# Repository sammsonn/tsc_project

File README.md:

# Nume: Samson Alexandru-Valentin
# Grupa: 332CC

## 1. Descriere Generala:
Acest repository contine fisierele de design hardware pentru proiectul OpenBook, un e-book reader ieftin si open source, generate in cadrul fazei EVT. Obiectivul acestei faze a fost transformarea specificatiilor de sistem intr-un design hardware functional si integrat mecanic, pregatit pentru fabricarea primelor prototipuri.

## Etapele Initiale ale Dezvoltarii EVT (Rezumat)

Dezvoltarea designului livrat aici a urmat cativa pasi cheie:

1.  **Clarificarea Specificatiilor si Planificarea:** Am inceput prin analiza detaliata a specificatiilor primite de la Arhitectul de Sistem pentru a intelege complet cerintele functionale, de performanta si de cost. Am adresat intrebari pentru clarificarea oricaror ambiguitati si am stabilit un plan de lucru initial. Tot in aceasta etapa am configurat mediul de dezvoltare in Fusion si repository-ul Git.

2.  **Selectia Componentelor si Crearea Librariilor:** Pe baza specificatiilor, am selectat componentele electronice specifice (Part Numbers), acordand o atentie deosebita costului, disponibilitatii pe termen lung si performantei. Pentru fiecare componenta aleasa, am creat sau validat librariile necesare in Fusion 360: simbolul schematic, footprint-ul PCB (conform datasheet) si, unde a fost posibil, modelul 3D asociat. Am inceput compilarea unui Bill of Materials (BOM) preliminar.

3.  **Captura Schematica (Schematic Capture):** Folosind librariile create, am desenat diagrama schematica in Fusion 360. Aceasta reprezinta conexiunile logice dintre toate componentele electronice. Am structurat schema pe module functionale (ex: Alimentare, Procesor, Memorie, Interfata Display, etc.) pentru claritate si am rulat verificari ERC (Electrical Rule Check) pentru a detecta erori de baza.

4.  **Proiectarea PCB (PCB Layout) - Faza Initiala:** Am inceput transpunerea schemei intr-un layout fizic pe placa de circuit imprimat (PCB). Aceasta a inclus definirea conturului placii (conform dimensiunilor impuse de carcasa), definirea structurii straturilor (layer stackup) si plasarea initiala a componentelor critice (conectori, circuite integrate principale, componente cu constrangeri mecanice), tinand cont de fluxul de semnal si constrangerile carcasei.

5.  **Modelare 3D si Integrare Mecanica Preliminara:** in paralel cu layout-ul PCB, am creat modele 3D simplificate, dar dimensional corecte, pentru elementele non-PCB majore (Display E-Ink, Baterie LiPo). Am inceput asamblarea virtuala in Fusion, combinand modelul 3D al PCB-ului (cu componentele plasate), modelele display-ului si bateriei, si modelul 3D al carcasei (primit) pentru a verifica potrivirea generala si a identifica potentiale conflicte de spatiu.

## 2. Diagrama Bloc

## 3. BOM - Bill of Materials
| Device | Value | Check_Price | Datasheet |
|--------|-------|-------------|-----------|
| ADAFRUIT_LEDCHIP-LED0603 | - | [Link](https://www.snapeda.com/parts/KP-1608SURCK/Kingbright/view-part/?ref=search&t=LED%200603) | [Link](https://www.snapeda.com/parts/KP-1608SURCK/Kingbright/datasheet/) |
| SJ | - | [Link](https://grabcad.com/library/solder-jumpers-1) | [Link](https://grabcad.com/library/solder-jumpers-1) |
| EAGLE-LTSPICE_C | 0.1uF/50V | [Link](https://componentsearchengine.com/part-view/CC0402MRX5R5BB106/YAGEO) | [Link](https://componentsearchengine.com/Datasheets/2/CC0402MRX5R5BB106.pdf) |
| ESP32_WROVER_EAGLE-LTSPICE_R | 0.47 | [Link](https://componentsearchengine.com/part-view/R0402%201%25%20100%20K%20(RC0402FR-07100KL)/YAGEO) | [Link](https://www.yageo.com/upload/media/product/products/datasheet/rchip/PYu-RC_Group_51_RoHS_L_12.pdf) |
| ESP32_WROVER_EAGLE-LTSPICE_R | 100K | [Link](https://componentsearchengine.com/part-view/R0402%201%25%20100%20K%20(RC0402FR-07100KL)/YAGEO) | [Link](https://www.yageo.com/upload/media/product/products/datasheet/rchip/PYu-RC_Group_51_RoHS_L_12.pdf) |
| EAGLE-LTSPICE_C | 100nF | [Link](https://componentsearchengine.com/part-view/CC0402MRX5R5BB106/YAGEO) | [Link](https://componentsearchengine.com/Datasheets/2/CC0402MRX5R5BB106.pdf) |
| RCL_CPOL-EUCT3528 | 100uF TANT | [Link](https://www.snapeda.com/parts/TAJB475K025RNJ/AVX/view-part/?ref=dk&t=capacitor%203528&con_ref=None) | [Link](https://s3.amazonaws.com/snapeda/datasheet/TAJB475K025RNJ_AVX.pdf) |
| ESP32_WROVER_EAGLE-LTSPICE_R | 10K | [Link](https://componentsearchengine.com/part-view/R0402%201%25%20100%20K%20(RC0402FR-07100KL)/YAGEO) | [Link](https://www.yageo.com/upload/media/product/products/datasheet/rchip/PYu-RC_Group_51_RoHS_L_12.pdf) |
| EAGLE-LTSPICE_C | 10uF | [Link](https://componentsearchengine.com/part-view/CC0402MRX5R5BB106/YAGEO) | [Link](https://componentsearchengine.com/Datasheets/2/CC0402MRX5R5BB106.pdf) |
| 112A-TAAR-R03_ATTEND | 112A-TAAR-R03_ATTEND | [Link](https://store.comet.srl.ro/Catalogue/Product/43497/) | [Link](https://store.comet.bg/download-file.php?id=8824) |
| ESP32_WROVER_EAGLE-LTSPICE_R | 15 | [Link](https://componentsearchengine.com/part-view/R0402%201%25%20100%20K%20(RC0402FR-07100KL)/YAGEO) | [Link](https://www.yageo.com/upload/media/product/products/datasheet/rchip/PYu-RC_Group_51_RoHS_L_12.pdf) |
| EAGLE-LTSPICE_C | 1uF | [Link](https://componentsearchengine.com/part-view/CC0402MRX5R5BB106/YAGEO) | [Link](https://componentsearchengine.com/Datasheets/2/CC0402MRX5R5BB106.pdf) |
| EAGLE-LTSPICE_C | 1uF/50V | [Link](https://componentsearchengine.com/part-view/CC0402MRX5R5BB106/YAGEO) | [Link](https://componentsearchengine.com/Datasheets/2/CC0402MRX5R5BB106.pdf) |
| ESP32_WROVER_EAGLE-LTSPICE_R | 2.2 | [Link](https://componentsearchengine.com/part-view/R0402%201%25%20100%20K%20(RC0402FR-07100KL)/YAGEO) | [Link](https://www.yageo.com/upload/media/product/products/datasheet/rchip/PYu-RC_Group_51_RoHS_L_12.pdf) |
| ESP32_WROVER_EAGLE-LTSPICE_R | 200 | [Link](https://componentsearchengine.com/part-view/R0402%201%25%20100%20K%20(RC0402FR-07100KL)/YAGEO) | [Link](https://www.yageo.com/upload/media/product/products/datasheet/rchip/PYu-RC_Group_51_RoHS_L_12.pdf) |
| ESP32_WROVER_SPARKFUN-DISCRETESEMI_MOSFET_PCH-DMG2305UX-7 | 20V/4.2A/52m?/1.4W | [Link](https://componentsearchengine.com/part-view/DMG2305UX-7/Diodes%20Incorporated) | [Link](https://www.diodes.com//assets/Datasheets/DMG2305UX.pdf) |
| ESP32_WROVER_EAGLE-LTSPICE_R | 2K | [Link](https://componentsearchengine.com/part-view/R0402%201%25%20100%20K%20(RC0402FR-07100KL)/YAGEO) | [Link](https://www.yageo.com/upload/media/product/products/datasheet/rchip/PYu-RC_Group_51_RoHS_L_12.pdf) |
| EAGLE-LTSPICE_C | 4.7uF | [Link](https://componentsearchengine.com/part-view/CC0402MRX5R5BB106/YAGEO) | [Link](https://componentsearchengine.com/Datasheets/2/CC0402MRX5R5BB106.pdf) |
| EAGLE-LTSPICE_C | 4.7uF/25V | [Link](https://componentsearchengine.com/part-view/CC0402MRX5R5BB106/YAGEO) | [Link](https://componentsearchengine.com/Datasheets/2/CC0402MRX5R5BB106.pdf) |
| ESP32_WROVER_EAGLE-LTSPICE_R | 5k1 | [Link](https://componentsearchengine.com/part-view/R0402%201%25%20100%20K%20(RC0402FR-07100KL)/YAGEO) | [Link](https://www.yageo.com/upload/media/product/products/datasheet/rchip/PYu-RC_Group_51_RoHS_L_12.pdf) |
| 744043680IND_4828-WE-TPC_WRE | 68uH | [Link](https://ro.mouser.com/ProductDetail/Wurth-Elektronik/744043680?qs=PGXP4M47uW6VkZq%252BkzjrHA%3D%3D&_gl=1*5xajdn*_ga*MzY2ODgyMjE4LjE3NDM2NzQxODk.*_ga_15W4STQT4T*MTc0Mzg3MzkxMy40LjAuMTc0Mzg3MzkxNi41Ny4wLjA.) | [Link](https://www.we-online.com/components/products/datasheet/744043680.pdf) |
| BD5229G-TR | BD5229G-TR | [Link](https://componentsearchengine.com/part-view/BD5229G-TR/ROHM%20Semiconductor) | [Link](https://datasheet.datasheetarchive.com/originals/distributors/Datasheets_SAMA/f2b9741ef86007909f138d561a359946.pdf) |
| ESP32_WROVER_BME680_BME680 | BME688 | [Link](https://www.snapeda.com/parts/BME680/Bosch/view-part/?welcome=home) | [Link](https://www.snapeda.com/parts/BME680/Bosch%20Sensortec/datasheet/) |
| BUTTON_CUSYOMV1V2 | BUTTON_CUSYOMV1V2 | [Link](https://industry.panasonic.com/global/en/products/control/switch/light-touch/number/evqpuj02k) | [Link](https://industry.panasonic.com/global/en/downloads?tab=catalog&small_g_cd=203&part_no=EVQPUJ02K) |
| CPH3225A | CPH3225A | [Link](https://www.snapeda.com/parts/CPH3225A/Seiko+Instruments/view-part/?ref=eda) | [Link](https://www.snapeda.com/parts/CPH3225A/Seiko+Instruments/view-part/?ref=eda ) |
| DS3231SN# | DS3231SN# | [Link](https://www.snapeda.com/parts/DS3231SN%23/Analog+Devices/view-part/?ref=eda) | [Link](https://www.snapeda.com/parts/DS3231SN%23/Analog+Devices/view-part/?ref=eda) |
| ESP32-C6-WROOM-1-N8 | ESP32-C6-WROOM-1-N8 | [Link](https://www.snapeda.com/parts/ESP32-C6-WROOM-1-N8/Espressif+Systems/view-part/?ref=eda) | [Link](https://www.snapeda.com/parts/ESP32-C6-WROOM-1-N8/Espressif+Systems/view-part/?ref=eda) |
| ESP32C6_VARISTORCN1812 | ESP32C6_VARISTORCN1812 | [Link](https://www.mouser.co.uk/ProductDetail/EPCOS-TDK/B72520T0350K062?qs=dEfas%2FXlABIszF52uu7vrg%3D%3D) | [Link](https://www.tdk-electronics.tdk.com/inf/75/db/CTVS_14/Surge_protection_series.pdf) |
| ESP32_WROVER_SPARKFUN-IC-POWER_MCP73831 | ESP32_WROVER_SPARKFUN-IC-POWER_MCP73831 | [Link](https://ro.mouser.com/ProductDetail/Microchip-Technology/MCP73831T-2ACI-OT?qs=yUQqVecv4qvbBQBGbHx0Mw%3D%3D) | [Link](https://ro.mouser.com/datasheet/2/268/MCP73831_Family_Data_Sheet_DS20001984H-3441711.pdf) |
| FH34SRJ-24S-0.5SH_99_ | FH34SRJ-24S-0.5SH_99_ | [Link](https://componentsearchengine.com/part-view/FH34SRJ-24S-0.5SH(99)/Hirose) | [Link](https://www.hirose.com/en/product/document?clcode=CL0580-1255-6-99&productname=FH34SRJ-24S-0.5SH(99)&series=FH34SRJ&documenttype=2DDrawing&lang=en&documentid=0000990903) |
| MAX17048G+T10 | MAX17048G+T10 | [Link](https://www.snapeda.com/parts/MAX17048G+T10/Analog+Devices/view-part/?ref=eda) | [Link](https://www.snapeda.com/parts/MAX17048G+T10/Analog+Devices/view-part/?ref=eda) |
| MBR0530. | MBR0530. | [Link](https://www.snapeda.com/parts/MBR0530/Onsemi/view-part/?ref=eda) | [Link](https://www.snapeda.com/parts/MBR0530/ON%20Semiconductor/datasheet/) |
| PGB1010603MR. | PGB1010603MR. | [Link](https://www.snapeda.com/parts/PGB1010603MR/Littelfuse/view-part/?ref=eda) | [Link](https://www.snapeda.com/parts/PGB1010603MR/Littelfuse%20Inc./datasheet/) |
| QWIIC_CONNECTORJS-1MM | QWIIC_RIGHT_ANGLE | [Link](https://www.digikey.lt/en/models/926710 ) | [Link](https://www.digikey.lt/en/models/926710) |
| SAMACSYS_PARTS_USB4110-GF-A | SAMACSYS_PARTS_USB4110-GF-A | [Link](https://componentsearchengine.com/part-view/USB4110-GF-A/GCT%20(GLOBAL%20CONNECTOR%20TECHNOLOGY)) | [Link](https://gct.co/files/drawings/usb4110.pdf) |
| ESP32_WROVER_AVX---SD0805S020S1R0_AVX_SD0805S020S1R0_0_0AVX_SD0805S020S1R0_0_0 | SD0805S020S1R0 | [Link](https://ro.mouser.com/ProductDetail/KYOCERA-AVX/SD0805S020S1R0?qs=jCA%252BPfw4LHbpkAoSnwrdjw%3D%3D) | [Link](http://datasheets.avx.com/schottky.pdf) |
| SI1308EDL-T1-GE3 | SI1308EDL-T1-GE3 | [Link](https://www.snapeda.com/parts/SI1308EDL-T1-GE3/Vishay+Siliconix/view-part/?ref=eda) | [Link](https://www.snapeda.com/parts/SI1308EDL-T1-GE3/Vishay+Siliconix/view-part/?ref=eda) |
| TPV1 | TPV1 | Custom made | - |
| USBLC6-2SC6Y | USBLC6-2SC6Y | [Link](https://www.snapeda.com/parts/USBLC6-2SC6Y/STMicroelectronics/view-part/?ref=eda) | [Link](https://www.snapeda.com/parts/USBLC6-2SC6Y/STMicroelectronics/view-part/?ref=eda) |
| W25Q512JVEIQ | W25Q512JVEIQ | [Link](https://www.snapeda.com/parts/W25Q512JVEIQ/Winbond+Electronics/view-part/?ref=eda) | [Link](https://www.snapeda.com/parts/W25Q512JVEIQ/Winbond+Electronics/view-part/?ref=eda) |
| XC6220A331MR-G | XC6220A331MR-G | [Link](https://componentsearchengine.com/part-view/XC6220A331MR-G/Torex) | [Link](https://product.torexsemi.com/system/files/series/xc6220.pdf) |

## 4. Arhitectura Hardware

Mai jos sunt detaliate componentele hardware esentiale si rolul lor in functionarea dispozitivului:

| Nr. | Componenta Principala                   |
|-----|------------------------------------------|
| 1   | Microcontroller – ESP32-C6-WROOM-1       |
| 2   | Ecran E-Ink – Waveshare WSH-13187, 7.5”  |
| 3   | Senzor Ambiental – Bosch BME688          |
| 4   | Sistem de Alimentare si Baterie          |
| 5   | Butoane de Control – 3x Tactile Switch   |
| 6   | Conector USB-C                           |
| 7   | Port Extensie Qwiic / STEMMA QT (I2C)    |
| 8   | Soclu MicroSD – Attend 112A-TAAR-R03     |
| 9   | Ceas Timp Real (RTC) – DS3231            |

### 4.1. Unitatea Centrala – Microcontroller ESP32-C6-WROOM-1

-   **Unitate de Procesare:** RISC-V 32-bit, frecventa 160MHz
-   **Memorie:** 512KB SRAM intern + 8MB memorie flash extern (model W25Q512JVEIQ)
-   **Optiuni de Comunicare:** Wi-Fi 6 (standard 802.11ax), Bluetooth 5 LE, interfata USB 2.0 Full-Speed
-   **Interfete Disponibile:** SPI, I2C, UART, multiple porturi GPIO
-   **Consum Energetic:** Sub 50µA in modul deep sleep; diverse moduri de consum redus implementate
-   **Functii de Securitate:** Include secure boot, criptare pentru memoria flash si accelerare hardware pentru criptografie

### 4.2. Afisajul Electronic – Ecran E-Ink Waveshare WSH-13187, 7.5”

-   **Rezolutie:** 800x480 pixeli, imagine monocroma
-   **Modalitate de Conectare:** Interfata SPI (4 fire) plus linii de control CS, DC, RST, BUSY
-   **Consum Energetic:** Aproximativ 15–25mA in timpul actualizarii imaginii; consum neglijabil in stare statica
-   **Motivul alegerii:** Consum de energie neglijabil cand imaginea este statica, ideal pentru un e-reader

### 4.3. Senzorul Ambiental Integrat – Bosch BME688

-   **Parametri Masurati:** Temperatura, Umiditate relativa, Presiune atmosferica, Indice al Calitatii Aerului (estimare eCO2, TVOC)
-   **Acuratete:** ±1°C pentru temperatura, ±3% pentru umiditate, ±1 hPa pentru presiune
-   **Modalitate de Conectare:** Interfata I2C (operare la 400kHz)
-   **Consum Energetic:** 2.1µA in standby, maxim 3.6mA in timpul masuratorilor active
-   **Motivul alegerii:** Solutie compacta multi-senzor, potrivita pentru monitorizarea conditiilor ambientale

### 4.4. Sistemul de Alimentare si Gestionarea Energiei

-   **Sursa de Energie:** Acumulator Li-Po de 3.7V cu o capacitate de 2500mAh
-   **Monitorizare Baterie:** Circuit integrat MAX17048 (comunica prin I2C)
-   **Circuit de Incarcare:** MCP73831 – permite incarcarea cu 5V/1A via portul USB-C
-   **Regulator de Tensiune:** LDO ce furnizeaza o tensiune stabila de 3.3V pentru intregul circuit
-   **Consum Total Estimativ:**
    -   In mod activ: intre 100 si 150mA
    -   In mod deep sleep: sub 50µA

### 4.5. Interfata cu Utilizatorul – 3x Butoane Tactile

-   **Model Buton:** Panasonic EVQ-Q2A03W
-   **Conectare Electrica:** Legate la pini GPIO, cu circuit de debounce hardware (filtru RC)
-   **Functionalitati Asignate:** Navigare prin meniuri, avansare/revenire pagina, confirmare actiuni

### 4.6. Conectorul USB-C

-   **Functionalitati Principale:** Incarcarea bateriei si transferul de date (conform standardului USB 2.0)
-   **Masuri de Protectie:** Protectie ESD integrata si terminatii conforme standardului
-   **Posibilitati Suplimentare:** Actualizari software OTA (Over-The-Air) via Wi-Fi sau actualizare firmware prin conexiune USB

### 4.7. Portul de Extensie Qwiic / STEMMA QT (I2C)

-   **Configuratie Pini:** VCC (Alimentare), GND (Masa), SDA (Date I2C), SCL (Ceas I2C)
-   **Scop/Beneficii:** Permite conectarea rapida a modulelor si senzorilor externi compatibili I2C

### 4.8. Soclul pentru Card MicroSD – Attend 112A-TAAR-R03

-   **Rol Principal:** Ofera spatiu de stocare extern (pentru carti electronice, fisiere jurnal, firmware etc.)
-   **Modalitate de Conectare:** Interfata SPI

### 4.9. Ceasul Timp Real (RTC) – DS3231

-   **Acuratete:** Deviatie maxima de ±2 parti per milion (ppm)
-   **Modalitate de Conectare:** Interfata I2C
-   **Alimentare de Backup:** Asigurata de un supercapacitor

---

### Protocoale de Comunicare si Interfete Utilizate

| Protocol/Interfata | Componente Conectate                                |
|--------------------|-----------------------------------------------------|
| **SPI**            | Ecran E-Paper, Memorie Flash externa, Card SD (SPI) |
| **I2C**            | Senzor BME688, Fuel Gauge MAX17048, RTC DS3231, Port Qwiic/Stemma |
| **USB**            | Incarcare si comunicatie de date via USB-C         |
| **GPIO**           | Butoane, Linii control afisaj, Activare incarcare   |

---

### Profil de Consum Energetic (Estimari)

| Stare/Componenta       | Consum Estimativ   |
|------------------------|--------------------|
| ESP32-C6 (mod activ)   | 80–100mA           |
| Actualizare E-Paper    | 15–25mA            |
| Senzor BME688 (activ)  | 3.6mA              |
| Fuel Gauge MAX17048    | ~50µA              |
| RTC DS3231             | 3.5mA / 1µA backup |
| Deep Sleep (Total)     | <50–100µA          |

---

### Specificatii Fizice si Constructive

-   **Marimi Fizice:** 175 x 114 x 10 mm
-   **Masa Dispozitivului:** Aproximativ 250g
-   **Material Carcasa:** ABS sau policarbonat, cu design ergonomic
-   **Montare Afisaj:** Integrat intr-un decupaj specific al carcasei
-   **Detalii de Fabricatie:** PCB cu 2 straturi, finisaj ENIG, carcasa obtinuta prin injectie de plastic

## 5. Pini utilizati pe ESP32-C6 si justificare

| Pin ESP32-C6 | Componenta / Semnal                | Justificare                                                              |
|--------------|-------------------------------------|--------------------------------------------------------------------------|
| GPIO1        | I2C SDA (BME688, MAX17048, DS3231, Qwiic) | Linie partajata I2C - economiseste pini si permite extinderea usoara a sistemului |
| GPIO2        | I2C SCL (BME688, MAX17048, DS3231, Qwiic) | Semnal de ceas I2C pentru toti senzorii si portul de extensie Qwiic     |
| GPIO5        | SPI MISO (E-Paper, Flash extern)    | Linie comuna de intrare date (Master In Slave Out) pentru SPI            |
| GPIO6        | SPI MOSI (E-Paper, Flash extern)    | Linie comuna de iesire date (Master Out Slave In) pentru SPI             |
| GPIO7        | SPI CLK                             | Semnal de ceas (Clock) pentru magistrala SPI                             |
| GPIO8        | E-Paper CS                          | Selecteaza (Chip Select) ecranul E-Paper pe magistrala SPI                |
| GPIO9        | E-Paper DC (Data/Command)           | Comuta intre modul de comanda si modul de date pentru E-Paper            |
| GPIO10       | E-Paper RST                         | Linie de reset hardware pentru ecranul E-Paper                           |
| GPIO11       | E-Paper BUSY                        | Indica starea display-ului (ocupat/liber)                                |
| GPIO12       | Button #1                           | Intrare digitala pentru butonul de navigare (ex: pagina inainte)         |
| GPIO13       | Button #2                           | Intrare digitala pentru butonul de navigare (ex: pagina inapoi)          |
| GPIO14       | Button #3                           | Intrare digitala pentru butonul de selectie sau optiuni                 |
| GPIO15       | MAX17048 ALERT (optional)           | Pin optional pentru alerta de nivel scazut al bateriei de la MAX17048     |
| GPIO16       | USB D+ (intern la USB PHY)          | Linie de date pozitiva USB 2.0 (pin dedicat pe ESP32-C6)                 |
| GPIO17       | USB D- (intern la USB PHY)          | Linie de date negativa USB 2.0 (pin dedicat pe ESP32-C6)                 |
| GPIO18       | LED Status (optional)               | Iesire pentru un LED de stare (ex: activitate Wi-Fi, incarcare, etc.)    |
| GPIO19       | SD Card CS                          | Selectare (Chip Select) pentru cardul microSD pe magistrala SPI           |
| GPIO20       | SD Card MISO                        | Linie de citire date (Master In Slave Out) de pe cardul microSD         |
| GPIO21       | SD Card MOSI                        | Linie de scriere date (Master Out Slave In) pe cardul microSD           |
| GPIO4        | SD Card CLK                         | Semnal de ceas (Clock) pentru cardul microSD (SPI)                       |

## 6. Probleme Intampinate
1) In etapa de modelare 3D, a aparut o dificultate majora: modelele 3D pentru rezistente si condensatoare nu se actualizau automat in proiectul PCB la utilizarea functiei 'Replace Package'. Solutia a fost adaugarea manuala a modelelor 3D personalizate pentru fiecare dintre aceste componente.

2) Dimensiunea pad-urilor pentru bobina si conectorul USB, asa cum erau definite initial in footprint, s-a dovedit a fi insuficienta pentru grosimea terminalelor/pinilor. A fost necesara marirea manuala a acestor pad-uri in footprint pentru a facilita procesul de lipire.

## 7. Observatii
Un proiect cu un volum de munca foarte mare, care in opinia mea depaseste valoarea de 2 puncte din nota finala. Timp estimat de lucru: ~80 ore.

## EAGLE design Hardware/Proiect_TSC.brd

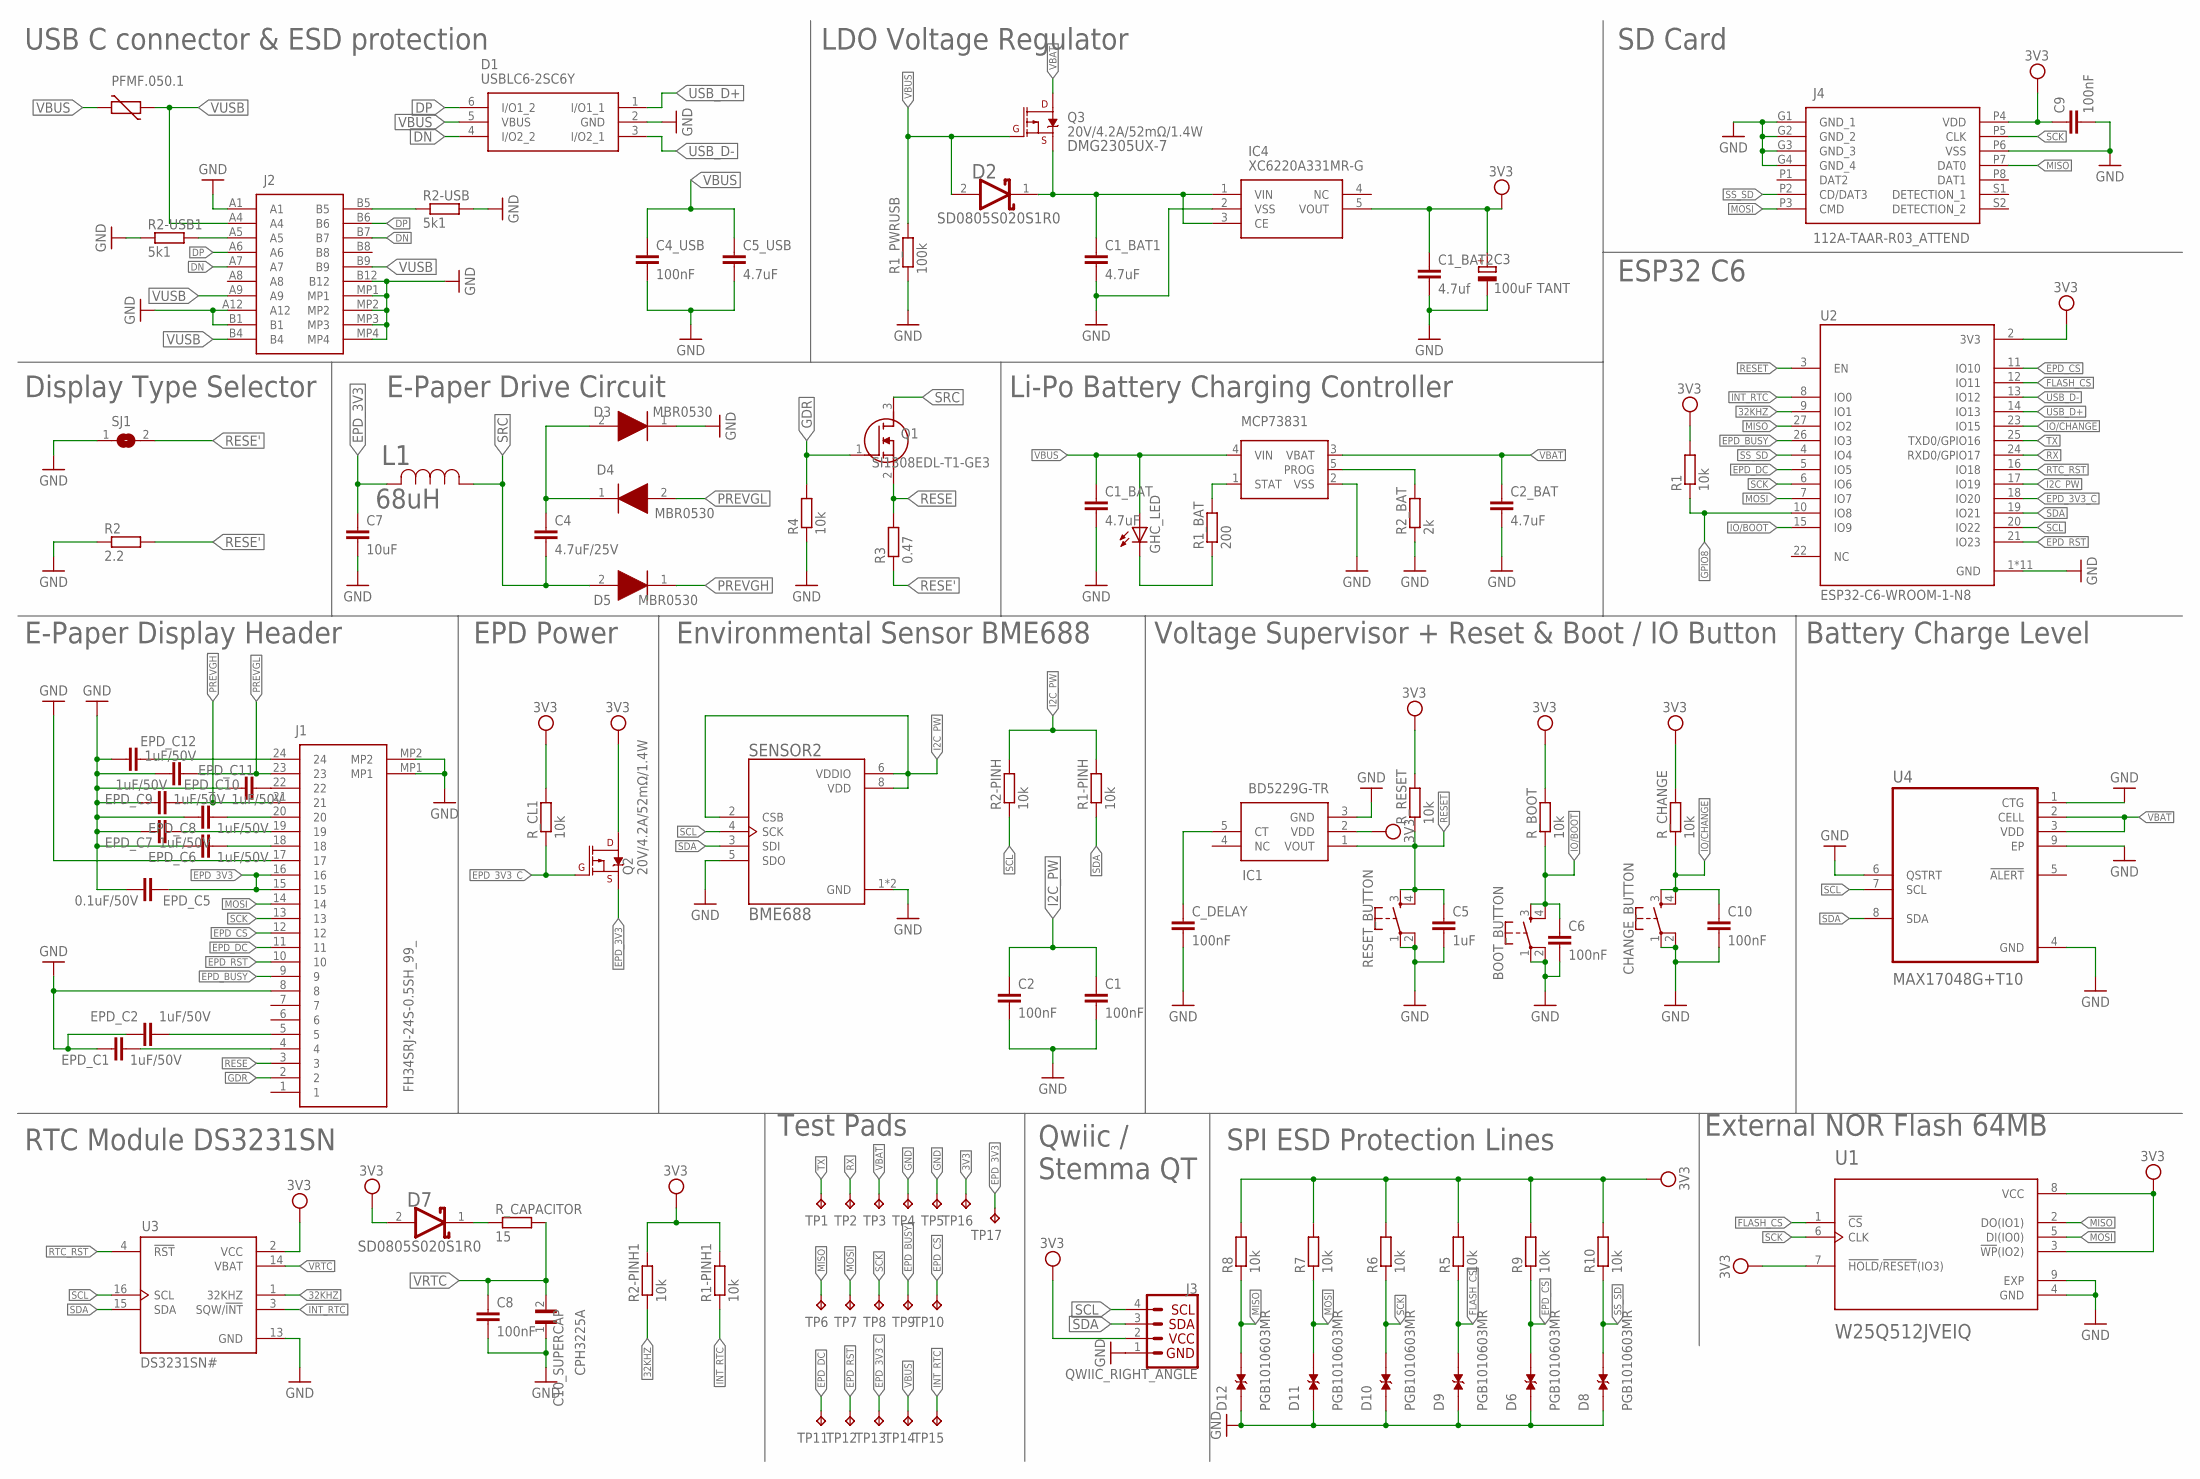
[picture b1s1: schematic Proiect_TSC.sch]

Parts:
BOOT_BUTTON: BUTTON_CUSYOMV1; MYBUTTON
C1, C2, C4_USB, C6, C8, C9, C10: 100nF; ESP32_WROVER_EAGLE-LTSPICE_C0402
C1_BAT, C1_BAT1, C2_BAT: 4.7uF; EAGLE-LTSPICE_C0402
C1_BAT2: 4.7uf; EAGLE-LTSPICE_C0402
C3: 100uF TANT; RCL_CT3528
C4: 4.7uF/25V; ESP32_WROVER_EAGLE-LTSPICE_C0402
C5: 1uF; ESP32_WROVER_EAGLE-LTSPICE_C0402
C5_USB: 4.7uF; ESP32_WROVER_EAGLE-LTSPICE_C0402
C7: 10uF; ESP32_WROVER_EAGLE-LTSPICE_C0402
C10_SUPERCAP: CPH3225A; CAPCP3225X100N
CHANGE_BUTTON: BUTTON_CUSYOMV1; MYBUTTON
C_DELAY: 100nF; ESP32_WROVER_EAGLE-LTSPICE_C0402
D1: USBLC6-2SC6Y; SOT95P280X145-6N
D2: SD0805S020S1R0; ESP32_WROVER_AVX---SD0805S020S1R0_AVX_SD0805S020S1R0_0
D3, D4, D5: MBR0530; SOD3716X135N
D6, D8, D9, D10, D11, D12: PGB1010603MR; DIOC1608X36N
D7: ESP32_WROVER_AVX---SD0805S020S1R0_AVX_SD0805S020S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; ESP32_WROVER_AVX---SD0805S020S1R0_AVX_SD0805S020S1R0_0
EPD_C1, EPD_C2, EPD_C6, EPD_C7, EPD_C8, EPD_C9, EPD_C10, EPD_C11, EPD_C12: 1uF/50V; ESP32_WROVER_EAGLE-LTSPICE_C0402
EPD_C5: 0.1uF/50V; ESP32_WROVER_EAGLE-LTSPICE_C0402
GHC_LED: ADAFRUIT_LEDCHIP-LED0603; ADAFRUIT_CHIP-LED0603
IC1: BD5229G-TR; SOT95P280X125-5N
IC4: XC6220A331MR-G; SOT95P280X120-5N
J1: FH34SRJ-24S-0.5SH_99_; FH34SRJ24S05SH99
J2: SAMACSYS_PARTS_USB4110-GF-A; SAMACSYS_PARTS_USB4110GFA
J3: QWIIC_RIGHT_ANGLE; JST04_1MM_RA
J4: 112A-TAAR-R03_ATTEND; 112ATAARR03ATTEND
L1: 68uH; IND_4828-WE-TPC_WRE
PFMF.050.1: ESP32C6_VARISTORCN1812; ESP32C6_VARISTOR_CT/CN1812
Q1: SI1308EDL-T1-GE3; SOT65P210X110-3N
Q2, Q3: 20V/4.2A/52mΩ/1.4W; ESP32_WROVER_SPARKFUN-DISCRETESEMI_SOT23-3
R1, R1-PINH, R1-PINH1, R2-PINH, R2-PINH1, R4, R5, R6, R7, R8, R9, R10: 10k; ESP32_WROVER_EAGLE-LTSPICE_R0402
R1_BAT: 200; ESP32_WROVER_EAGLE-LTSPICE_R0402
R1_PWRUSB: 100k; ESP32_WROVER_EAGLE-LTSPICE_R0402
R2: 2.2; ESP32_WROVER_EAGLE-LTSPICE_R0402
R2-USB, R2-USB1: 5k1; ESP32_WROVER_EAGLE-LTSPICE_R0402
R2_BAT: 2k; ESP32_WROVER_EAGLE-LTSPICE_R0402
R3: 0.47; ESP32_WROVER_EAGLE-LTSPICE_R0402
RESET_BUTTON: BUTTON_CUSYOMV1; MYBUTTON
R_BOOT: 10k; ESP32_WROVER_EAGLE-LTSPICE_R0402
R_CAPACITOR: 15; ESP32_WROVER_EAGLE-LTSPICE_R0402
R_CHANGE: 10k; ESP32_WROVER_EAGLE-LTSPICE_R0402
R_CL1: 10k; ESP32_WROVER_EAGLE-LTSPICE_R0402
R_RESET: 10k; ESP32_WROVER_EAGLE-LTSPICE_R0402
SENSOR2: BME688; ESP32_WROVER_BME680_PSON80P300X300X100-8N
SJ1: SJ
TP1, TP2, TP3, TP4, TP5, TP6, TP7, TP8, TP9, TP10, TP11, TP12, TP13, TP14, TP15, TP16, TP17: TPTP20R; TP20R
U: MCP73831; ESP32_WROVER_SPARKFUN-IC-POWER_SOT23-5
U1: W25Q512JVEIQ; SON127P600X800X80-9N
U2: ESP32-C6-WROOM-1-N8; XCVR_ESP32-C6-WROOM-1-N8
U3: DS3231SN#; SOIC127P1032X265-16N
U4: MAX17048G+T10; SON50P200X200X80-9N

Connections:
3V3: C1_BAT2.1, C3.+, C9.1, D7.2 (ANODE), IC1.2 (VDD), IC4.5 (VOUT), J3.2, J4.P4 (VDD), Q2.3 (D), R1.2, R1-PINH1.2, R2-PINH1.2, R5.2, R6.2, R7.2, R8.2, R9.2, R10.2, R_BOOT.2, R_CHANGE.2, R_CL1.2, R_RESET.2, TP16.TP, U1.3 (!WP!(IO2)), U1.7 (!HOLD!/!RESET!(IO3)), U1.8 (VCC), U2.2 (3V3), U3.2 (VCC)
32KHZ: R2-PINH1.1, U2.9 (IO1), U3.1 (32KHZ)
DN: D1.4 (I/O2_2), J2.A7, J2.B7
DP: D1.6 (I/O1_2), J2.A6, J2.B6
EPD_3V3: C7.1, EPD_C5.2, J1.15, J1.16, L1.2, Q2.2 (S), TP17.TP
EPD_3V3_C: Q2.1 (G), R_CL1.1, TP13.TP, U2.18 (IO20)
EPD_BUSY: J1.9, TP9.TP, U2.26 (IO3)
EPD_CS: D6.2, J1.12, R9.1, TP10.TP, U2.11 (IO10)
EPD_DC: J1.11, TP11.TP, U2.5 (IO5)
EPD_RST: J1.10, TP12.TP, U2.21 (IO23)
FLASH_CS: D9.2, R5.1, U1.1 (!CS), U2.12 (IO11)
GDR: J1.2, Q1.1 (G), R4.2
GND: BOOT_BUTTON.1, BOOT_BUTTON.2, C1.2, C1_BAT.2, C1_BAT1.2, C1_BAT2.2, C2.2, C2_BAT.2, C3.-, C4_USB.2, C5.2, C5_USB.2, C6.2, C7.2, C8.2, C9.2, C10.2, C10_SUPERCAP.1, CHANGE_BUTTON.1, CHANGE_BUTTON.2, C_DELAY.2, D1.2 (GND), D3.1 (K), D6.1, D8.1, D9.1, D10.1, D11.1, D12.1, EPD_C1.1, EPD_C2.1, EPD_C5.1, EPD_C6.1, EPD_C7.1, EPD_C8.1, EPD_C9.1, EPD_C10.1, EPD_C11.1, EPD_C12.1, IC1.3 (GND), IC4.2 (VSS), J1.8, J1.17, J1.MP1, J1.MP2, J2.A1, J2.A12, J2.B1, J2.B12, J2.MP1, J2.MP2, J2.MP3, J2.MP4, J3.1, J4.G1 (GND_1), J4.G2 (GND_2), J4.G3 (GND_3), J4.G4 (GND_4), J4.P6 (VSS), R1_PWRUSB.1, R2.1, R2-USB.2, R2-USB1.1, R2_BAT.1, R4.1, RESET_BUTTON.1, RESET_BUTTON.2, SENSOR2.1 (GND), SENSOR2.5 (SDO), SENSOR2.7 (GND), SJ1.1, TP4.TP, TP5.TP, U.2 (VSS), U1.4 (GND), U1.9 (EXP), U2.1 (GND), U2.28 (GND), U2.29_1 (GND), U2.29_2 (GND), U2.29_3 (GND), U2.29_4 (GND), U2.29_5 (GND), U2.29_6 (GND), U2.29_7 (GND), U2.29_8 (GND), U2.29_9 (GND), U3.13 (GND), U4.1 (CTG), U4.4 (GND), U4.6 (QSTRT), U4.9 (EP)
GPIO8: R1.1, U2.10 (IO8)
I2C_PW: C1.1, C2.1, R1-PINH.2, R2-PINH.2, SENSOR2.2 (CSB), SENSOR2.6 (VDDIO), SENSOR2.8 (VDD), U2.17 (IO19)
INT_RTC: R1-PINH1.1, TP15.TP, U2.8 (IO0), U3.3 (SQW/!INT)
IO/BOOT: BOOT_BUTTON.3, BOOT_BUTTON.4, C6.1, R_BOOT.1, U2.15 (IO9)
IO/CHANGE: C10.1, CHANGE_BUTTON.3, CHANGE_BUTTON.4, R_CHANGE.1, U2.23 (IO15)
MISO: D12.2, J4.P7 (DAT0), R8.1, TP6.TP, U1.2 (DO(IO1)), U2.27 (IO2)
MOSI: D11.2, J1.14, J4.P3 (CMD), R7.1, TP7.TP, U1.5 (DI(IO0)), U2.7 (IO7)
unnamed: J2.A5, R2-USB1.2
unnamed: J2.B5, R2-USB.1
unnamed: C4.1, D3.2 (A), D4.1 (K)
unnamed: EPD_C2.2, J1.5
unnamed: EPD_C1.2, J1.4
unnamed: EPD_C6.2, J1.18
unnamed: EPD_C8.2, J1.20
unnamed: EPD_C7.2, J1.19
unnamed: EPD_C12.2, J1.24
unnamed: EPD_C10.2, J1.22
unnamed: D7.1 (CATHODE), R_CAPACITOR.1
unnamed: C1_BAT1.1, D2.1 (CATHODE), IC4.1 (VIN), IC4.3 (CE), Q3.2 (S)
unnamed: R1_BAT.2, U.1 (STAT)
unnamed: GHC_LED.C, R1_BAT.1
unnamed: C_DELAY.1, IC1.5 (CT)
unnamed: R2_BAT.2, U.5 (PROG)
PREVGH: D5.1 (K), EPD_C9.2, J1.21
PREVGL: D4.2 (A), EPD_C11.2, J1.23
RESE: J1.3, Q1.2 (S), R3.2
RESE': R2.2, R3.1, SJ1.2
RESET: C5.1, IC1.1 (VOUT), RESET_BUTTON.3, RESET_BUTTON.4, R_RESET.1, U2.3 (EN)
RTC_RST: U2.16 (IO18), U3.4 (!RST)
RX: TP2.TP, U2.24 (RXD0/GPIO17)
SCK: D10.2, J1.13, J4.P5 (CLK), R6.1, TP8.TP, U1.6 (CLK), U2.6 (IO6)
SCL: J3.4, R2-PINH.1, SENSOR2.4 (SCK), U2.20 (IO22), U3.16 (SCL), U4.7 (SCL)
SDA: J3.3, R1-PINH.1, SENSOR2.3 (SDI), U2.19 (IO21), U3.15 (SDA), U4.8 (SDA)
SRC: C4.2, D5.2 (A), L1.1, Q1.3 (D)
SS_SD: D8.2, J4.P2 (CD/DAT3), R10.1, U2.4 (IO4)
TX: TP1.TP, U2.25 (TXD0/GPIO16)
USB_D+: D1.1 (I/O1_1), U2.14 (IO13)
USB_D-: D1.3 (I/O2_1), U2.13 (IO12)
VBAT: C2_BAT.1, Q3.3 (D), TP3.TP, U.3 (VBAT), U4.2 (CELL), U4.3 (VDD)
VBUS: C1_BAT.1, C4_USB.1, C5_USB.1, D1.5 (VBUS), D2.2 (ANODE), GHC_LED.A, PFMF.050.1.2, Q3.1 (G), R1_PWRUSB.2, TP14.TP, U.4 (VIN)
VRTC: C8.1, C10_SUPERCAP.2, R_CAPACITOR.2, U3.14 (VBAT)
VUSB: J2.A4, J2.A9, J2.B4, J2.B9, PFMF.050.1.1

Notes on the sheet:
USB C connector & ESD protection
LDO Voltage Regulator
SD Card
Display Type Selector
E-Paper Drive Circuit
Li-Po Battery Charging Controller
ESP32 C6
Battery Charge Level
Voltage Supervisor + Reset & Boot / IO Button
Environmental Sensor BME688
EPD Power
E-Paper Display Header
RTC Module DS3231SN
Test Pads
Qwiic / Stemma QT
SPI ESD Protection Lines
External NOR Flash 64MB
SD0805S020S1R0
DMG2305UX-7

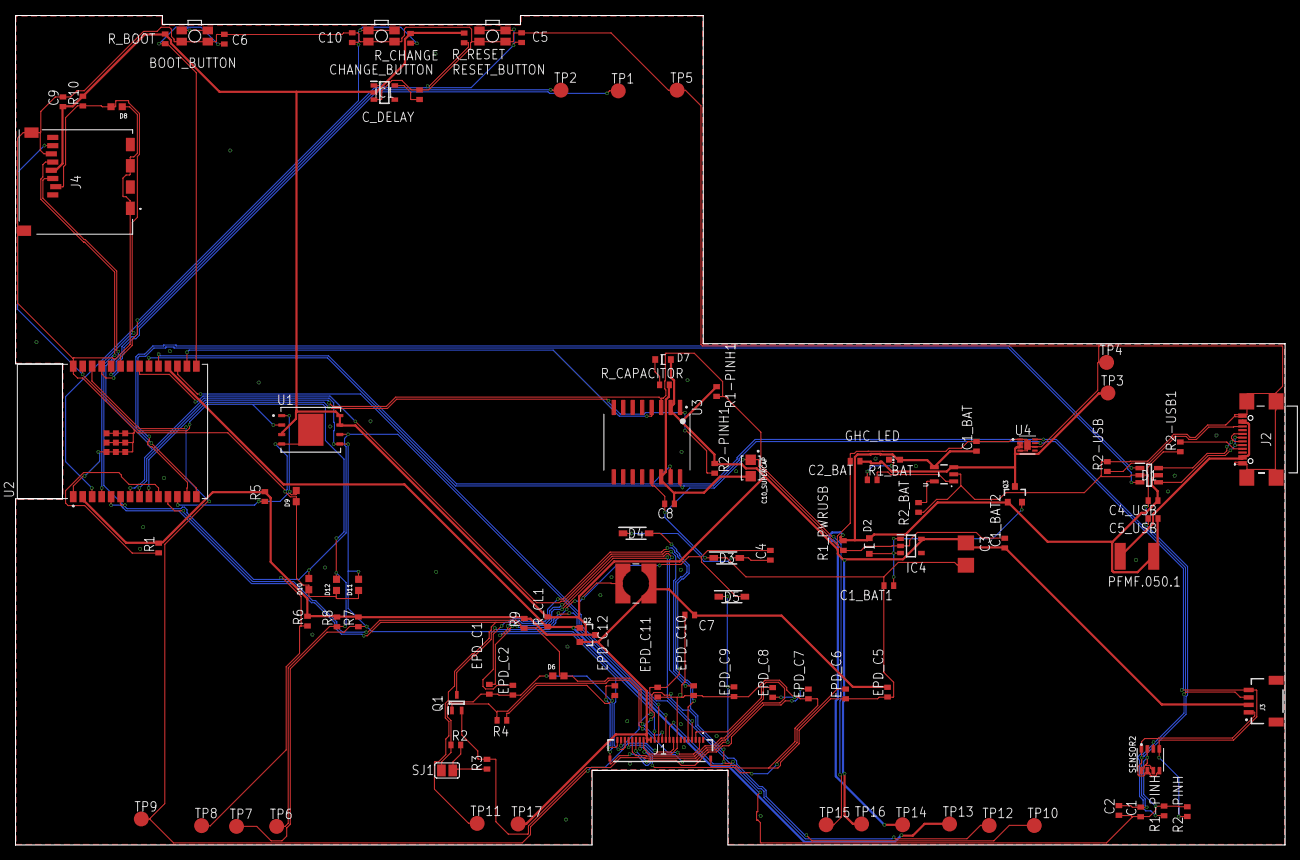
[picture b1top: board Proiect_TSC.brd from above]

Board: 2 copper layers, 170.2 x 111.2 mm, 103 parts (0 on the bottom side), 55 nets.

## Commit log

2025-04-13 Solved all open issues. Updated images and README.

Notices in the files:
parts and their libraries:
COPYRIGHT: Copyright (C) 2024 Ultra Librarian. All rights reserved.
